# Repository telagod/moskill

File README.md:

<h1 align="center">MosKill</h1>
<p align="center">
  <strong>Smart Mosquito Swatter with BLE, Kill Counting & Statistics</strong><br/>
  <em>ESP32-C3 Firmware + KiCad PCB + UniApp Cross-Platform Client</em>
</p>

<p align="center">

</p>

---

## System Architecture

## Features

- **Kill Detection** — Current pulse analysis, 4-class classification (S Fruit Fly / M Mosquito / L House Fly / XL Moth)
- **Statistics Engine** — Total kills, streak records, hourly heatmap, size distribution, efficiency scoring
- **Environment Correlation** — AHT20 temp/humidity sensing, mosquito activity vs. environment cross-analysis
- **BLE 5.0** — Real-time kill notifications, stats read, device config, OTA firmware update
- **UI Feedback** — WS2812B color-coded kill effects, streak rainbow animation, buzzer sound FX
- **Power Management** — 18650 Li-ion USB-C charging, 5-min auto deep sleep (5uA)
- **Cross-Platform App** — WeChat Mini Program / Android / iOS / H5, i18n (zh/en), dev mode
- **Fully AI-Designed** — From empty directory to manufacturable Gerber, zero human intervention

## PCB Design

30 x 100 mm narrow strip designed to fit inside a mosquito swatter handle. 91 components, dual-layer with full GND pour.

<p align="center">
  
  &nbsp;&nbsp;&nbsp;&nbsp;
  
  &nbsp;&nbsp;&nbsp;&nbsp;
  
  &nbsp;&nbsp;&nbsp;&nbsp;
  
</p>
<p align="center"><em>Left to right: 3D Top, 3D Bottom, Flat Top, Flat Bottom</em></p>

## Hardware

| Component | Part | Function |
|-----------|------|----------|
| MCU | ESP32-C3-MINI-1 | RISC-V 160MHz, BLE 5.0, 4MB Flash |
| HV Boost | NE555 + AO3400 + EE13 Transformer (10:200) | 3.7V -> ~2000V DC |
| HV Multiplier | 3-stage Cockcroft-Walton (UF4007 + 1nF/2kV) | Voltage tripler |
| Current Sense | 0.1ohm + LMV358 (Gain=20) + BAT43 Peak Det | Kill waveform capture |
| Env Sensor | AHT20 (I2C) | Temp +/-0.3C / Humidity +/-2%RH |
| Power | 18650 + TP4056 + ME6211 LDO | USB-C charging, 3.3V regulated |
| Battery Protect | DW01A + FS8205A | Over-charge/discharge/current protection |
| LED | WS2812B | RGB status + kill effects |
| Buzzer | KCG0601 Passive Piezo | Kill sound FX + streak rising tone |

> Full schematic: [`hardware/kicad/moskill.kicad_sch`](hardware/kicad/moskill.kicad_sch) | BOM: [`hardware/bom/BOM.csv`](hardware/bom/BOM.csv) | Gerber: [`hardware/kicad/moskill-gerbers.zip`](hardware/kicad/moskill-gerbers.zip)

## Project Structure

```
moskill/
├── firmware/                        # ESP-IDF v5.4 firmware (938KB binary)
│   ├── main/                        # Entry point, 6 FreeRTOS tasks
│   └── components/
│       ├── kill_detector/           # 4-state kill detection FSM
│       ├── stats_engine/            # Statistics + NVS sharded storage
│       ├── ble_service/             # BLE GATT server + OTA handler
│       ├── env_sensor/              # AHT20 I2C driver (thread-safe)
│       ├── power_mgmt/             # Battery curve, HV control, deep sleep
│       └── hv_driver/              # WS2812B RMT driver
├── hardware/
│   ├── kicad/                       # KiCad 9 schematic + PCB (30x100mm)
│   ├── bom/BOM.csv                  # 48 line items, ~¥24.48
│   └── renders/                     # 3D and flat PCB renders
├── app/                             # UniApp cross-platform client
│   └── src/
│       ├── pages/                   # 7 pages (dashboard, stats, rank, control, ota, ...)
│       ├── components/MkIcon.vue    # SVG icon component (38 icons)
│       ├── utils/
│       │   ├── ble.js               # BLE communication layer (128-bit UUIDs)
│       │   ├── icons.js             # SVG icon definitions
│       │   ├── i18n.js              # Chinese/English auto-switch
│       │   └── mock.js              # Dev mode mock data generator
│       └── store/index.js           # Vuex state management
├── protocol/ble_protocol.md         # BLE GATT protocol specification
├── tools/ble_debug/                 # Python BLE debug tool (bleak + rich)
└── docs/DESIGN.md                   # Full system design document
```

## Build Firmware

```bash
# Install ESP-IDF v5.4+
# https://docs.espressif.com/projects/esp-idf/en/latest/esp32c3/get-started/

cd firmware
idf.py set-target esp32c3
idf.py build                         # -> build/moskill.bin (938KB)
idf.py -p /dev/ttyUSB0 flash monitor
```

## Build App

```bash
cd app
npm install
npx uni build                        # H5 build
npx uni build -p mp-weixin           # WeChat Mini Program
npx uni dev:h5                       # H5 dev server

# Dev mode: no device needed, uses mock data for UI development
```

## Kill Detection Pipeline

```
ADC 1kHz sampling -> Threshold trigger -> Sustain check (>=5ms)
    -> Peak capture -> Envelope match -> Classification -> Stats update
    -> BLE notify -> LED + Buzzer feedback

Classification by peak ADC:
  S  (< 800)    Fruit Fly
  M  (800-2000) Mosquito
  L  (2000-3200) House Fly
  XL (> 3200)   Moth / Beetle
```

## BLE Protocol

128-bit custom UUIDs (base `e3a1XXXX-f5e8-4c8a-9b3d-2c1f7b8a6d50`), packed wire format for efficiency.

| Service | UUID Short | Description |
|---------|-----------|-------------|
| MosKill Main | `0x1B00` | Kill count (notify), session/lifetime stats, kill log, environment |
| Config | `0x1B11` | Sensitivity, LED, buzzer, streak effects + time sync |
| OTA | `0x1B21` | Firmware update (start/write/verify/abort with CRC32) |
| Battery | `0x180F` | Standard Battery Service |

> Full protocol spec: [`protocol/ble_protocol.md`](protocol/ble_protocol.md)

## BLE Debug Tool

```bash
cd tools/ble_debug
pip install -r requirements.txt

python moskill_ble.py scan                          # Scan devices
python moskill_ble.py stats <ADDR>                  # Read statistics
python moskill_ble.py monitor <ADDR>                # Real-time kill monitor
python moskill_ble.py config <ADDR> -s 2 -b 3      # Set sensitivity/buzzer
python moskill_ble.py ota <ADDR> firmware.bin       # BLE OTA update
```

## License

MIT

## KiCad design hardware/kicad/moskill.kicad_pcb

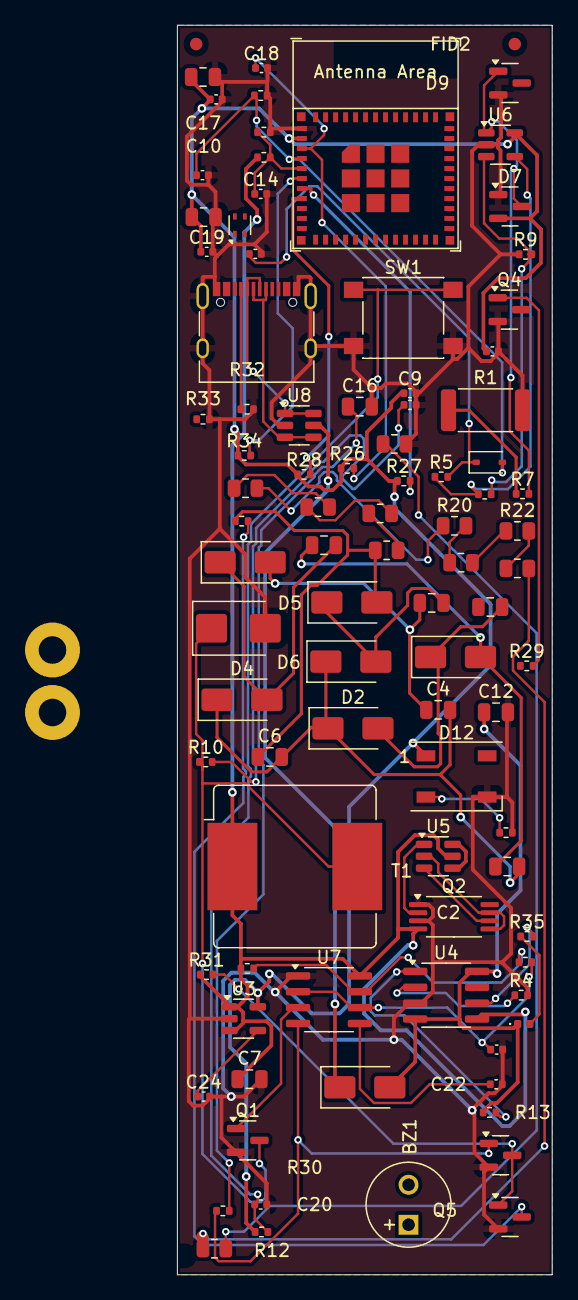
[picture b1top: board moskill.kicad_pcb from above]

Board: 2 copper layers, 30.0 x 100.0 mm, 95 parts (1 on the bottom side), 58 nets.

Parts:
BZ1: Buzzer; MagneticBuzzer_Kingstate_KCG0601
C1, C2, C3, C4, C5, C6: 1nF/2kV; C_0805_2012Metric
C7, C10, C16, C17: 10uF; C_0805_2012Metric
C8, C9, C11, C14, C18, C19, C20: 100nF; C_0402_1005Metric
C12: 4.7uF; C_0805_2012Metric
C13: 1uF; C_0402_1005Metric
C15: 1nF; C_0402_1005Metric
C21, C22, C23: 10nF; C_0402_1005Metric
C24: 100pF; C_0402_1005Metric
D1, D2, D3, D4, D5, D6: UF4007; D_SMA
D7: BAT54S; SOT-23
D8: BAT43; D_SOD-323
D9: BZX84C3V3; SOT-23
D10: SMBJ24A; D_SMB
D11: SS34; D_SMA
D12: WS2812B; LED_WS2812B_PLCC4_5.0x5.0mm_P3.2mm
D13: LED_STDBY; LED_0402_1005Metric
FID1, FID2, FID3: Fiducial; Fiducial_1mm_Mask2mm
H1, H2: M2; MountingHole_2.2mm_M2_Pad
J1: USB-C; USB_C_Receptacle_XKB_U262-16XN-4BVC11
Q1: AO3400A; SOT-23
Q2: FS8205A; TSSOP-8_4.4x3mm_P0.65mm
Q3, Q4, Q5: 2N7002; SOT-23
R1: 0R1_2W; R_2512_6332Metric
R2, R3, R13, R15, R26, R30, R31, R34: 10K; R_0402_1005Metric
R4: 2K; R_0402_1005Metric
R5: 1.5K; R_0402_1005Metric
R6, R12: 100K; R_0402_1005Metric
R7, R9, R35: 1K; R_0402_1005Metric
R8: 19K; R_0402_1005Metric
R10, R11, R29, R36: 100R; R_0402_1005Metric
R14, R27, R28: 4.7K; R_0402_1005Metric
R16, R17, R18, R19, R20, R21, R22, R23, R24, R25: 1M; R_0805_2012Metric
R32, R33: 5.1K; R_0402_1005Metric
SW1: Button; SW_SPST_PTS645
T1: EE13 1:20; L_Bourns_SRR1208_12.7x12.7mm
U1A: ESP32-C3-L; ESP32-C3-MINI-1
U2: AHT20; Sensirion_DFN-4_1.5x1.5mm_P0.8mm_SHT4x_NoCentralPad
U3: ME6211C33; SOT-23-5
U4: TP4056; SOIC-8_3.9x4.9mm_P1.27mm
U5: DW01A; SOT-23-6
U6: LMV321/LMV358; SOT-23-5
U7: NE555; SOIC-8_3.9x4.9mm_P1.27mm
U8: USBLC6-2SC6; SOT-23-6

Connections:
+3V3: C8.1, C9.1, C10.1, C11.1, C17.1, C19.1, D7.2, D12.1, R26.1, R27.1, R28.1, R30.1, R34.1, U1A.2, U2.1, U3.5, U6.5
+5V_PROT: C12.1, D11.2, D13.1, R13.1, U4.4, U4.8
+BATT: C7.1, Q2.4, Q2.8, R2.1, R14.1, R31.1, T1.1, U3.1, U3.3, U4.5, U5.5, U7.8
ADC_SENSE: C13.1, D8.2, R6.1, U1A.4
BLD_0: R16.2, R17.1
BLD_1: R17.2, R18.1
BLD_2: R18.2, R19.1
BLD_3: R19.2, R20.1
BLD_4: R20.2, R21.1
BLD_5: R21.2, R22.1
BLD_6: R22.2, R23.1
BLD_7: R23.2, R24.1
BLD_8: R24.2, R25.1
BOOT: R34.2, U1A.6
BTN_IN: C20.1, R30.2, SW1.1
BUZ_GATE: Q4.1, R29.2
CC1: J1.A5, R32.1
CC2: J1.B5, R33.1
CS_SENSE: Q2.5, Q2.7, U5.2
CW_N1: C1.2, D1.1, D2.2
CW_N2: C2.1, C3.1, D1.2
CW_N3: C3.2, D3.1, D4.2
CW_N4: C4.1, C5.1, D3.2
CW_N5: C5.2, D5.1, D6.2
DISCH_DRN: Q3.3, R11.2
EN: C18.1, R26.2, U1A.3
FILT_OUT: C23.1, D8.1, R5.2
GND: C7.2, C8.2, C9.2, C10.2, C11.2, C12.2, C13.2, C14.2, C15.2, C16.2, C17.2, C18.2, C19.2, C20.2, C21.2, C22.2, C23.2, C24.2, D7.1, D9.2, D10.2, D12.3, J1.A1, J1.A12, J1.B1, J1.B12, J1.S1, Q1.2, Q2.1, Q2.3, Q3.2, Q4.2, Q5.2, R1.2, R3.2, R4.2, R6.2, R9.1, R25.2, R32.2, R33.2, R36.2, SW1.2, U1A.1, U2.3, U3.2, U4.3, U6.2, U7.1, U8.2
GND_BAT: U5.4, U5.6
HV_EN: Q5.1, R12.1, U7.4
HV_EN_INV: Q3.1, Q5.3, R31.2
HV_EN_RC: C16.1, R12.2
HV_OUT: C6.1, D5.2, R11.1, R16.1
HV_RET: R1.1, R7.1
HV_SEC_BOT: C2.2, C4.2, C6.2, D2.1, D4.1, D6.1
I2C_SCL: R28.2, U1A.8, U2.4
I2C_SDA: R27.2, U1A.7, U2.2
LDO_BP: C24.1, U3.4
LED_DOUT_RAW: D12.2, R36.1
NE555_CV: C22.1, U7.5
NE555_DIS: R14.2, R15.1, U7.7
NE555_OUT: Q1.1, U7.3
NE555_THR_TR: C21.1, R15.2, U7.2, U7.6
OC: Q2.6, U5.3
OD: Q2.2, U5.1
OPAMP_INM: R8.2, R9.2, U6.3
OPAMP_OUT: R5.1, R8.1, U6.4
PROG: R4.1, U4.2
Q1_DRAIN: D10.1, Q1.3, R10.1, T1.2
SENSE_LIM: D7.3, D9.1, R7.2, U6.1
SNUB_M: C15.1, R10.2
STDBY_LED: D13.2, R35.1
STDBY_OUT: R35.2, U4.6
TEMP_TP: R13.2, U4.1
USB_DM: J1.A7, J1.B7, U8.1, U8.6
USB_DP: J1.A6, J1.B6, U8.3, U8.4
VBAT_SENSE: C14.1, R2.2, R3.1, U1A.5
VBUS: D11.1, J1.A4, J1.A9, J1.B4, J1.B9, U8.5

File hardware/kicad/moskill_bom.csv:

"Refs","Value","Footprint","Qty","DNP"
"BZ1","Buzzer","Buzzer_Beeper:Buzzer_12x9.5RM7.6","1",""
"C1","1nF/2kV","Capacitor_SMD:C_0805_2012Metric","1",""
"C2","1nF/2kV","Capacitor_SMD:C_0805_2012Metric","1",""
"C3","1nF/2kV","Capacitor_SMD:C_0805_2012Metric","1",""
"C4","1nF/2kV","Capacitor_SMD:C_0805_2012Metric","1",""
"C5","1nF/2kV","Capacitor_SMD:C_0805_2012Metric","1",""
"C6","1nF/2kV","Capacitor_SMD:C_0805_2012Metric","1",""
"C7","10uF","Capacitor_SMD:C_0805_2012Metric","1",""
"C8","100nF","Capacitor_SMD:C_0402_1005Metric","1",""
"C9","100nF","Capacitor_SMD:C_0402_1005Metric","1",""
"C10","10uF","Capacitor_SMD:C_0805_2012Metric","1",""
"C11","100nF","Capacitor_SMD:C_0402_1005Metric","1",""
"C12","4.7uF","Capacitor_SMD:C_0805_2012Metric","1",""
"C13","1uF","Capacitor_SMD:C_0402_1005Metric","1",""
"C14","100nF","Capacitor_SMD:C_0402_1005Metric","1",""
"C15","1nF","Capacitor_SMD:C_0402_1005Metric","1",""
"C16","10uF","Capacitor_SMD:C_0805_2012Metric","1",""
"C17","10uF","Capacitor_SMD:C_0805_2012Metric","1",""
"C18","100nF","Capacitor_SMD:C_0402_1005Metric","1",""
"C19","100nF","Capacitor_SMD:C_0402_1005Metric","1",""
"C20","100nF","Capacitor_SMD:C_0402_1005Metric","1",""
"C21","10nF","Capacitor_SMD:C_0402_1005Metric","1",""
"C22","10nF","Capacitor_SMD:C_0402_1005Metric","1",""
"C23","10nF","Capacitor_SMD:C_0402_1005Metric","1",""
"C24","100pF","Capacitor_SMD:C_0402_1005Metric","1",""
"D1","UF4007","Diode_SMD:D_SMA","1",""
"D2","UF4007","Diode_SMD:D_SMA","1",""
"D3","UF4007","Diode_SMD:D_SMA","1",""
"D4","UF4007","Diode_SMD:D_SMA","1",""
"D5","UF4007","Diode_SMD:D_SMA","1",""
"D6","UF4007","Diode_SMD:D_SMA","1",""
"D7","BAT54S","Package_TO_SOT_SMD:SOT-23","1",""
"D8","BAT43","Diode_SMD:D_SOD-323","1",""
"D9","BZX84C3V3","Package_TO_SOT_SMD:SOT-23","1",""
"D10","SMBJ24A","Diode_SMD:D_SMB","1",""
"D11","SS34","Diode_SMD:D_SMA","1",""
"D12","WS2812B","LED_SMD:LED_WS2812B_PLCC4_5.0x5.0mm_P3.2mm","1",""
"D13","LED_STDBY","LED_SMD:LED_0402_1005Metric","1",""
"J1","USB-C","Connector_USB:USB_C_Receptacle_XKB_U262-16XN-4BVC11","1",""
"Q1","AO3400A","Package_TO_SOT_SMD:SOT-23","1",""
"Q2","FS8205A","Package_SO:TSSOP-8_4.4x3mm_P0.65mm","1",""
"Q3","2N7002","Package_TO_SOT_SMD:SOT-23","1",""
"Q4","2N7002","Package_TO_SOT_SMD:SOT-23","1",""
"Q5","2N7002","Package_TO_SOT_SMD:SOT-23","1",""
"R1","0R1_2W","Resistor_SMD:R_2512_6332Metric","1",""
"R2","10K","Resistor_SMD:R_0402_1005Metric","1",""
"R3","10K","Resistor_SMD:R_0402_1005Metric","1",""
"R4","2K","Resistor_SMD:R_0402_1005Metric","1",""
"R5","1.5K","Resistor_SMD:R_0402_1005Metric","1",""
"R6","100K","Resistor_SMD:R_0402_1005Metric","1",""
"R7","1K","Resistor_SMD:R_0402_1005Metric","1",""
"R8","19K","Resistor_SMD:R_0402_1005Metric","1",""
"R9","1K","Resistor_SMD:R_0402_1005Metric","1",""
"R10","100R","Resistor_SMD:R_0402_1005Metric","1",""
"R11","100R","Resistor_SMD:R_0402_1005Metric","1",""
"R12","100K","Resistor_SMD:R_0402_1005Metric","1",""
"R13","10K","Resistor_SMD:R_0402_1005Metric","1",""
"R14","4.7K","Resistor_SMD:R_0402_1005Metric","1",""
"R15","10K","Resistor_SMD:R_0402_1005Metric","1",""
"R16","1M","Resistor_SMD:R_0805_2012Metric","1",""
"R17","1M","Resistor_SMD:R_0805_2012Metric","1",""
"R18","1M","Resistor_SMD:R_0805_2012Metric","1",""
"R19","1M","Resistor_SMD:R_0805_2012Metric","1",""
"R20","1M","Resistor_SMD:R_0805_2012Metric","1",""
"R21","1M","Resistor_SMD:R_0805_2012Metric","1",""
"R22","1M","Resistor_SMD:R_0805_2012Metric","1",""
"R23","1M","Resistor_SMD:R_0805_2012Metric","1",""
"R24","1M","Resistor_SMD:R_0805_2012Metric","1",""
"R25","1M","Resistor_SMD:R_0805_2012Metric","1",""
"R26","10K","Resistor_SMD:R_0402_1005Metric","1",""
"R27","4.7K","Resistor_SMD:R_0402_1005Metric","1",""
"R28","4.7K","Resistor_SMD:R_0402_1005Metric","1",""
"R29","100R","Resistor_SMD:R_0402_1005Metric","1",""
"R30","10K","Resistor_SMD:R_0402_1005Metric","1",""
"R31","10K","Resistor_SMD:R_0402_1005Metric","1",""
"R32","5.1K","Resistor_SMD:R_0402_1005Metric","1",""
"R33","5.1K","Resistor_SMD:R_0402_1005Metric","1",""
"R34","10K","Resistor_SMD:R_0402_1005Metric","1",""
"R35","1K","Resistor_SMD:R_0402_1005Metric","1",""
"R36","100R","Resistor_SMD:R_0402_1005Metric","1",""
"SW1","Button","Button_Switch_SMD:SW_SPST_PTS645","1",""
"T1","EE13 1:20","Inductor_SMD:L_Bourns_SRR1208_12.7x12.7mm","1",""
"U1A?","ESP32-C3-L","Espressif:ESP32-C3-MINI-1","1",""
"U1B?","ESP32-C3-R","Espressif:ESP32-C3-MINI-1","1",""
"U2","AHT20","Sensor_Humidity:Sensirion_DFN-4_1.5x1.5mm_P0.8mm_SHT4x_NoCentralPad","1",""
"U3","ME6211C33","Package_TO_SOT_SMD:SOT-23-5","1",""
"U4","TP4056","Package_SO:SOIC-8_3.9x4.9mm_P1.27mm","1",""
"U5","DW01A","Package_TO_SOT_SMD:SOT-23-6","1",""
"U6","LMV321/LMV358","Package_TO_SOT_SMD:SOT-23-5","1",""
"U7","NE555","Package_SO:SOIC-8_3.9x4.9mm_P1.27mm","1",""
"U8","USBLC6-2SC6","Package_TO_SOT_SMD:SOT-23-6","1",""

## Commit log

2026-06-09 feat: MosKill smart mosquito swatter - full product release v1.0.0
    Complete AI-automated hardware product:
    - ESP32-C3 firmware (ESP-IDF v5.4, FreeRTOS, BLE 5.0 GATT)
    - KiCad 9 PCB (30x100mm, 91 components, Gerber ready for JLCPCB)
    - UniApp cross-platform app (Vue 3, 7 pages, SVG icons, i18n zh/en, dev mode)
    - HV boost circuit (NE555 + EE13 transformer, 3-stage Cockcroft-Walton ~2000V)
    - Kill detection (current pulse sensing, 4-class classification S/M/L/XL)
2026-06-09 fix: include Espressif KiCad library files (was tracked as empty submodule)
    107 files: symbols, footprints, 3D models for ESP32-C3-MINI-1
2026-06-09 docs: overhaul README with images, architecture diagram, and updated specs
    - Brand logo SVG centered at top
    - System architecture SVG diagram (HV circuit, MCU, peripherals, app)
    - PCB render images (3D + flat, top + bottom)
    - Badge bar (ESP32-C3, BLE 5.0, KiCad 9, UniApp, HV, BOM cost)
    - Updated specs: KiCad 9, 30x100mm, EE13, AO3400, 128-bit UUIDs
    - Added UniApp build section and dev mode instructions
2026-06-09 fix(pcb): net class differentiation, power/HV trace widening, fiducials, GND pour
    Layout review rework (3.3/10 → improved):
    - Net classes: HV (0.25mm/0.4mm clearance), Power (0.3mm/0.25mm),
    Analog (0.2mm/0.3mm), Signal (0.2mm/0.2mm default)
    - Trace distribution: 45% signal 0.2mm, 11% HV 0.25mm, 42% power 0.3mm
    (was 93% uniform 0.2mm)
    - 3 fiducials (FID1/FID2/FID3) for SMT pick-and-place
2026-06-09 docs: update PCB render images after layout rework
    High-quality KiCad 9 ray-traced renders (1200x3600, high quality):
    - 3D top/bottom with perspective
    - Flat top/bottom orthographic
    Reflects net class widening, fiducials, and re-routed traces.
2026-06-09 fix(renders): re-render with distinct angles - 3D tilted 45° with floor shadows vs flat orthographic
2026-06-09 fix(pcb): fix 3D model paths KICAD6/7→KICAD9, .wrl→.step — renders now show components
2026-06-09 fix(pcb): resolve all 90 missing 3D models for proper rendering
    - ESP32-C3-MINI-1 → ESP32-C3-WROOM-02 (closest KiCad 9 match)
    - USB-C XKB → GCT USB4085 (generic USB-C receptacle)
    - SW_SPST_PTS645 → PTS645Sx43SMTR92 (exact match with suffix)
    - EE13 transformer → Bourns SRP6060FA (inductor placeholder)
    - AHT20 → HDC2080 (DFN humidity sensor placeholder)
    All 90 model paths now resolve to existing .step files.
2026-06-09 fix(3d): use exact ESP32-C3-MINI-1 STEP from Espressif lib, remove mismatched USB-C/transformer/AHT20 placeholders
2026-06-09 fix(3d): correct ESP32-C3-MINI-1 model alignment, clean orphaned tags
